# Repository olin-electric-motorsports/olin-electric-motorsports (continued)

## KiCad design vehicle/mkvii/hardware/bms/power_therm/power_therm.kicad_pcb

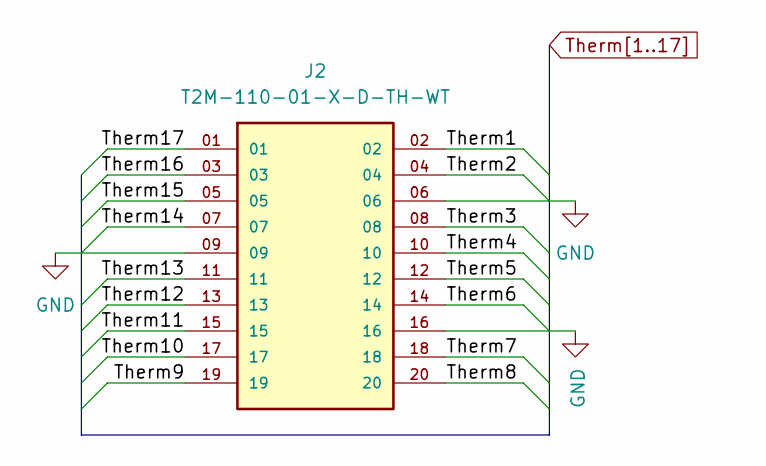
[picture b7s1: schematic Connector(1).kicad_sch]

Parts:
J2: T2M-110-01-X-D-TH-WT; SAMTEC_T2M-110-01-X-D-TH-WT; PARTREV AH

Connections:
Therm1: J2.02; also elsewhere on the board
Therm2: J2.04; also elsewhere on the board
Therm3: J2.08; also elsewhere on the board
Therm4: J2.10; also elsewhere on the board
Therm5: J2.12; also elsewhere on the board
Therm6: J2.14; also elsewhere on the board
Therm7: J2.18; also elsewhere on the board
Therm8: J2.20; also elsewhere on the board
Therm9: J2.19; also elsewhere on the board
Therm10: J2.17; also elsewhere on the board
Therm11: J2.15; also elsewhere on the board
Therm12: J2.13; also elsewhere on the board
Therm13: J2.11; also elsewhere on the board
Therm14: J2.07; also elsewhere on the board
Therm15: J2.05; also elsewhere on the board
Therm16: J2.03; also elsewhere on the board
Therm17: J2.01; also elsewhere on the board

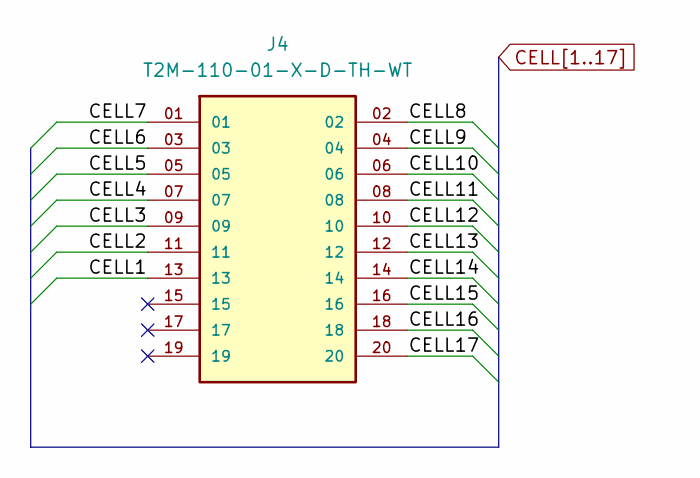
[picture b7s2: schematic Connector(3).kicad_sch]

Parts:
J4: T2M-110-01-X-D-TH-WT; SAMTEC_T2M-110-01-X-D-TH-WT; PARTREV AH

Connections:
CELL1: J4.13; also elsewhere on the board
CELL2: J4.11; also elsewhere on the board
CELL3: J4.09; also elsewhere on the board
CELL4: J4.07; also elsewhere on the board
CELL5: J4.05; also elsewhere on the board
CELL6: J4.03; also elsewhere on the board
CELL7: J4.01; also elsewhere on the board
CELL8: J4.02; also elsewhere on the board
CELL9: J4.04; also elsewhere on the board
CELL10: J4.06; also elsewhere on the board
CELL11: J4.08; also elsewhere on the board
CELL12: J4.10; also elsewhere on the board
CELL13: J4.12; also elsewhere on the board
CELL14: J4.14; also elsewhere on the board
CELL15: J4.16; also elsewhere on the board
CELL16: J4.18; also elsewhere on the board
CELL17: J4.20; also elsewhere on the board

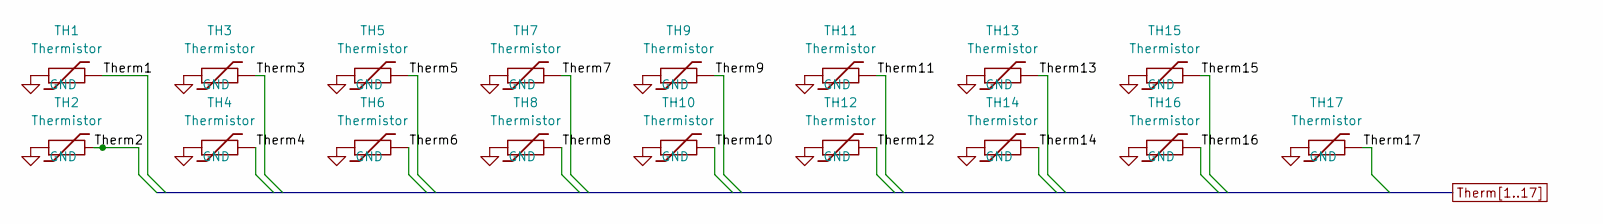
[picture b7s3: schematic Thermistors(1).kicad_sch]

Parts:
TH1, TH2, TH3, TH4, TH5, TH6, TH7, TH8, TH9, TH10, TH11, TH12, TH13, TH14, TH15, TH16, TH17: Thermistor; R_0603

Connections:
Therm1: TH1.2; also elsewhere on the board
Therm2: TH2.2; also elsewhere on the board
Therm3: TH3.2; also elsewhere on the board
Therm4: TH4.2; also elsewhere on the board
Therm5: TH5.2; also elsewhere on the board
Therm6: TH6.2; also elsewhere on the board
Therm7: TH7.2; also elsewhere on the board
Therm8: TH8.2; also elsewhere on the board
Therm9: TH9.2; also elsewhere on the board
Therm10: TH10.2; also elsewhere on the board
Therm11: TH11.2; also elsewhere on the board
Therm12: TH12.2; also elsewhere on the board
Therm13: TH13.2; also elsewhere on the board
Therm14: TH14.2; also elsewhere on the board
Therm15: TH15.2; also elsewhere on the board
Therm16: TH16.2; also elsewhere on the board
Therm17: TH17.2; also elsewhere on the board

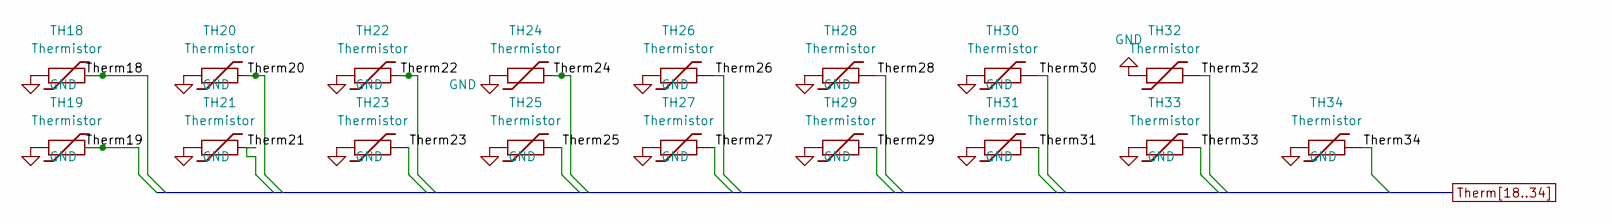
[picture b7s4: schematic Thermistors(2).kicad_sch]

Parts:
TH18, TH19, TH20, TH21, TH22, TH23, TH24, TH25, TH26, TH27, TH28, TH29, TH30, TH31, TH32, TH33, TH34: Thermistor; R_0603

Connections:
Therm18: TH18.2; also elsewhere on the board
Therm19: TH19.2; also elsewhere on the board
Therm20: TH20.2; also elsewhere on the board
Therm21: TH21.2; also elsewhere on the board
Therm22: TH22.2; also elsewhere on the board
Therm23: TH23.2; also elsewhere on the board
Therm24: TH24.2; also elsewhere on the board
Therm25: TH25.2; also elsewhere on the board
Therm26: TH26.2; also elsewhere on the board
Therm27: TH27.2; also elsewhere on the board
Therm28: TH28.2; also elsewhere on the board
Therm29: TH29.2; also elsewhere on the board
Therm30: TH30.2; also elsewhere on the board
Therm31: TH31.2; also elsewhere on the board
Therm32: TH32.2; also elsewhere on the board
Therm33: TH33.2; also elsewhere on the board
Therm34: TH34.2; also elsewhere on the board

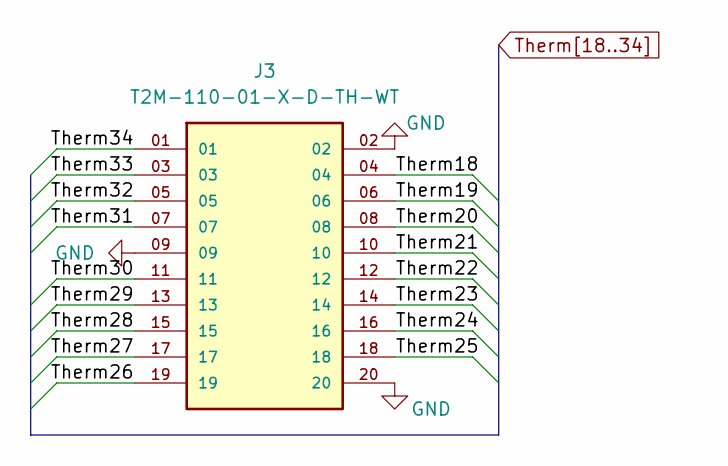
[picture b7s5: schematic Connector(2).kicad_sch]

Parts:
J3: T2M-110-01-X-D-TH-WT; SAMTEC_T2M-110-01-X-D-TH-WT; PARTREV AH

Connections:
Therm18: J3.02; also elsewhere on the board
Therm19: J3.04; also elsewhere on the board
Therm20: J3.08; also elsewhere on the board
Therm21: J3.10; also elsewhere on the board
Therm22: J3.12; also elsewhere on the board
Therm23: J3.14; also elsewhere on the board
Therm24: J3.18; also elsewhere on the board
Therm25: J3.20; also elsewhere on the board
Therm26: J3.19; also elsewhere on the board
Therm27: J3.17; also elsewhere on the board
Therm28: J3.15; also elsewhere on the board
Therm29: J3.13; also elsewhere on the board
Therm30: J3.11; also elsewhere on the board
Therm31: J3.07; also elsewhere on the board
Therm32: J3.05; also elsewhere on the board
Therm33: J3.03; also elsewhere on the board
Therm34: J3.01; also elsewhere on the board

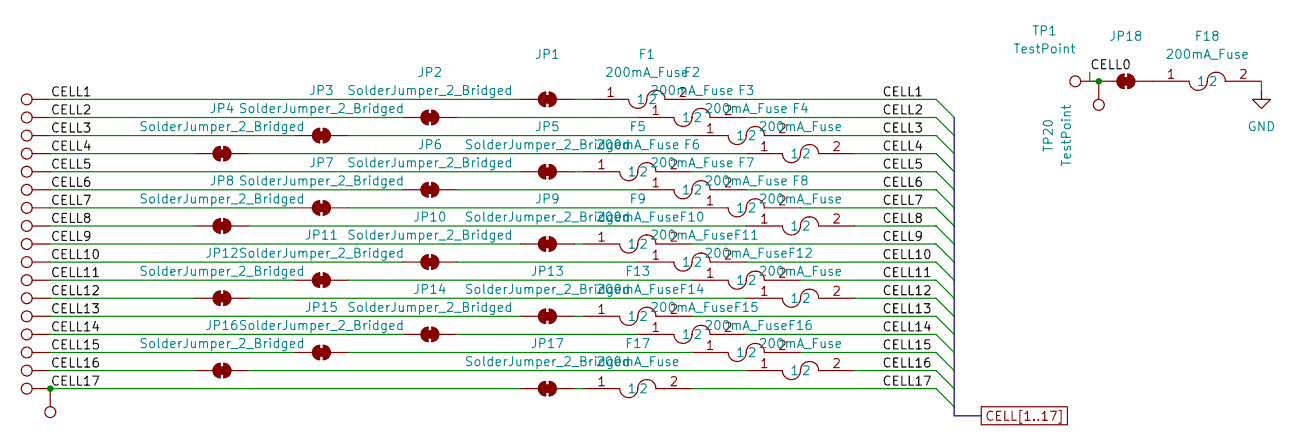
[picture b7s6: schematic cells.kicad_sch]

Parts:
F1, F2, F3, F4, F5, F6, F7, F8, F9, F10, F11, F12, F13, F14, F15, F16, F17, F18: 200mA_Fuse; Fuse_0805_2012Metric; MPN 507-1767-1-ND
JP1, JP2, JP3, JP4, JP5, JP6, JP7, JP8, JP9, JP10, JP11, JP12, JP13, JP14, JP15, JP16, JP17, JP18: SolderJumper_2_Bridged; SolderJumper-2_P1.3mm_Bridged2Bar_Pad1.0x1.5mm
TP1, TP2: TestPoint; Wurth-7461115
TP3, TP4, TP5, TP6, TP7, TP8, TP9, TP10, TP11, TP12, TP13, TP14, TP15, TP16, TP17, TP18, TP19, TP20: TestPoint; Bond Pad(4p)

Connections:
/Cells/CELL0: JP18.1 (A), TP1.1, TP20.1
CELL1: F1.2, JP1.1 (A), TP3.1; also elsewhere on the board
CELL2: F2.2, JP2.1 (A), TP4.1; also elsewhere on the board
CELL3: F3.2, JP3.1 (A), TP5.1; also elsewhere on the board
CELL4: F4.2, JP4.1 (A), TP6.1; also elsewhere on the board
CELL5: F5.2, JP5.1 (A), TP7.1; also elsewhere on the board
CELL6: F6.2, JP6.1 (A), TP8.1; also elsewhere on the board
CELL7: F7.2, JP7.1 (A), TP9.1; also elsewhere on the board
CELL8: F8.2, JP8.1 (A), TP10.1; also elsewhere on the board
CELL9: F9.2, JP9.1 (A), TP11.1; also elsewhere on the board
CELL10: F10.2, JP10.1 (A), TP12.1; also elsewhere on the board
CELL11: F11.2, JP11.1 (A), TP13.1; also elsewhere on the board
CELL12: F12.2, JP12.1 (A), TP14.1; also elsewhere on the board
CELL13: F13.2, JP13.1 (A), TP15.1; also elsewhere on the board
CELL14: F14.2, JP14.1 (A), TP16.1; also elsewhere on the board
CELL15: F15.2, JP15.1 (A), TP17.1; also elsewhere on the board
CELL16: F16.2, JP16.1 (A), TP18.1; also elsewhere on the board
CELL17: F17.2, JP17.1 (A), TP2.1, TP19.1; also elsewhere on the board
unnamed: F1.1, JP1.2 (B)
unnamed: F2.1, JP2.2 (B)
unnamed: F3.1, JP3.2 (B)
unnamed: F4.1, JP4.2 (B)
unnamed: F5.1, JP5.2 (B)
unnamed: F6.1, JP6.2 (B)
unnamed: F7.1, JP7.2 (B)
unnamed: F8.1, JP8.2 (B)
unnamed: F9.1, JP9.2 (B)
unnamed: F10.1, JP10.2 (B)
unnamed: F11.1, JP11.2 (B)
unnamed: F12.1, JP12.2 (B)
unnamed: F13.1, JP13.2 (B)
unnamed: F14.1, JP14.2 (B)
unnamed: F15.1, JP15.2 (B)
unnamed: F16.1, JP16.2 (B)
unnamed: F17.1, JP17.2 (B)
unnamed: F18.1, JP18.2 (B)

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
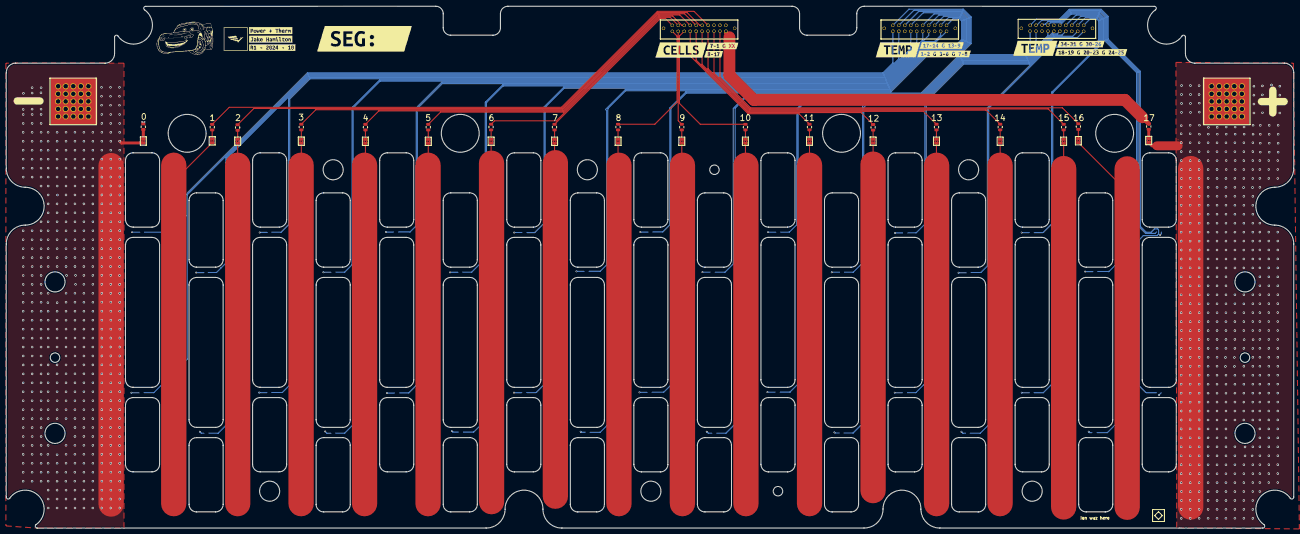
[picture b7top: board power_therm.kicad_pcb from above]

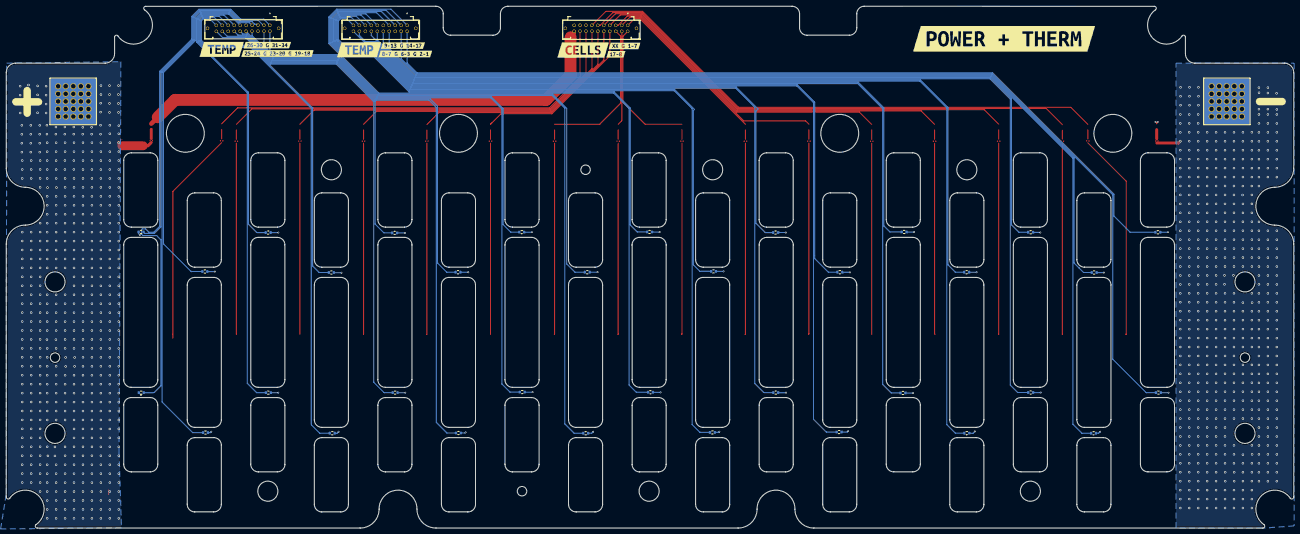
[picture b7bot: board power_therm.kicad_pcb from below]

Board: 4 copper layers, 431.8 x 175.0 mm, 116 parts (49 on the bottom side), 71 nets.

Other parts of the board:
kibuzzard-6738FA22, kibuzzard-6738FA22#2: G***; kibuzzard-6738FA22
kibuzzard-6738FB07: G***; kibuzzard-6738FB07
kibuzzard-6738FB8F: G***; kibuzzard-6738FB8F
kibuzzard-6738FB72, kibuzzard-6738FB72#2, kibuzzard-6738FB72#3, kibuzzard-6738FB72#4: G***; kibuzzard-6738FB72
kibuzzard-6738FBE8: G***; kibuzzard-6738FBE8
kibuzzard-6738FCFE: G***; kibuzzard-6738FCFE
kibuzzard-6738FD11: G***; kibuzzard-6738FD11
kibuzzard-6738FEC0: G***; kibuzzard-6738FEC0
kibuzzard-6738FEC9: G***; kibuzzard-6738FEC9
kibuzzard-6738FED3: G***; kibuzzard-6738FED3
kibuzzard-6738FF3D: G***; kibuzzard-6738FF3D
kibuzzard-6738FF8B: G***; kibuzzard-6738FF8B
kibuzzard-6738FFDD: G***; kibuzzard-6738FFDD
kibuzzard-6738FFEC: G***; kibuzzard-6738FFEC
kibuzzard-6739182D: G***; kibuzzard-6739182D
kibuzzard-67390047: G***; kibuzzard-67390047
kibuzzard-67390054: G***; kibuzzard-67390054
kibuzzard-67390064: G***; kibuzzard-67390064
kibuzzard-67391881: G***; kibuzzard-67391881
